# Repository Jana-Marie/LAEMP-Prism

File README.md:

# LAEMP-Prism

The LÄMP-Prism is an aesthetically pleasing and colorful effect lamp that can be used in your home. It can be controlled using Zigbee (e.g., Philips Hue) and has RGBY + WW/CW LEDs, providing a wide dynamic range and fantastic color representation. The lamp can be soldered together at home or assembled by JLCPCB.

An inbuilt slow fade-animation creates plenty colored dots around the room, one can choose from three different animations by quickly bringing red from 0% to 100% and back three times. LAEMP will switch from static light, to slow-fading dots to being an RGB-beacon. Its most pleasing mode is the slow-fading animation. It is fast enough to raise the rooms texture, slow enough to not be irritating and just perfect for comfy nights.

The project consists of nine PCBs that are cleverly interlocked with pinheaders and capacitors. The Prism-like shape, combined with its 291 LEDs, projects a slightly changing dotted pattern into its environment.

<table>
  <tbody>
    <tr>
      <td>
        
      </td>
      <td>
        
      </td>
    </tr>
  </tbody>
</table>

This project is an attempt to add some colored lights and interesting patterns to ones home. I hope you enjoy it! :3

<table>
  <tbody>
    <tr>
      <td>
        
      </td>
      <td>
        
      </td>
    </tr>
  </tbody>
</table>

### V2

Please note that the E75-2G4M20S module is End of Life and is hard to obtain. I'm working on a V2.0 with STM32WB (see [MiniBee](https://github.com/Jana-Marie/MiniBee)). The Hex-Base-Board is henceforth subject to be updated, all other boards shouldnt change.

### Sister project

LAEMP-Prism is a sister project to [LAEMP-Panel](https://github.com/Jana-Marie/LAEMP-Panel)

## Concept

The overall concept was developed in OpenSCAD and a pseudo-random pattern of circles was choosen for the walls. If one wants to put effort into this project, different walls can be used. The standard base-to-wall-interface also allows for much different and custom walls. E.g. hexagonal holes, shorter or taller walls, bended walls, ...

## Build

This build is definitely time-consuming, as each LAEMP Prism features 291 LEDs, and therefore requires at least 291 100nF capacitors. Additionally, the wall PCBs are rather thin and long, making reflow difficult and assembly time-consuming.

Once all eight boards are assembled (the top board has no components ^⁻^), they can be interlocked with one another. To do this, begin by plugging the LED-Base-Board into the Base-Board, and then carefully plugging wall after wall into the baseboard. Try to put the Top-Board onto the build after assembling five boards. The board with the Type-C cutout should not be the last board to assemble. Finally, try to plug in the last board. This step can be quite tricky and may require a few attempts. Once all boards are assembled, align all walls with each other and place the whole board onto the 3D printed base.

You will need the following set of baords for a build:

 - 1 x Base-Board
 - 1 x Base-LED-Board
 - 1 x Top-Board
 - 5 x Wall-Board
 - 1 x USB-Wall-Board

<table>
  <tbody>
    <tr>
      <td>
        
      </td>
      <td>
        
      </td>
    </tr>
    <tr>
      <td>
        
      </td>
      <td>
        
      </td>
    </tr>
  </tbody>
</table>

## Firmware

There are two firmwares to be flashed, one for the ESP32 and one for the E75-2G4M20S.

### ESP32

This is a simple Arduino project and can be flashed via Arduino (initially built on Arduino 1.8.19).

### E75

Please refer to the awesome works of [PeeVeeOne](https://peeveeone.com/zll-tldr/) to flash `Light_ColorLight_JN5168_RGB` onto the E75-2G4M20S module.

## Todo

 - [ ] Bug: Animation selector sucks, it gets stuck on states, needs fix.
 - [ ] Bug: Color wheel is off
 - [ ] Update to baseboard v2

## Folder Structure

```
 - 3D/               3D-Printable base, Concept
 - design/           assets, renders
 - images/           images for README
 - laemp_base/       base board hosting the MCU(s)
 - laemp_led_board/  LED base board, plugs directly ontop of the base board
 - laemp_top/        top board, has no electrical functionality, just mechanical
 - laemp_wall/       wall board, hosting 41 leds each
 - laemp_wall_usb/   same wall board, but with USB cutout
 - firmware/
   - leamp_prism/    ESP32 FW
   - zigbee/         E75 FW
```

## License

Copyright Jana Marie Hemsing 2023.
This source describes Open Hardware and is licensed under the CERN-
OHL-S v2.

You may redistribute and modify this source and make products using it
under the terms of the CERN-OHL-S v2
([LICENSE](/LICENSE)).

This source is distributed WITHOUT ANY EXPRESS OR IMPLIED
WARRANTY, INCLUDING OF MERCHANTABILITY, SATISFACTORY
QUALITY AND FITNESS FOR A PARTICULAR PURPOSE. Please see
the CERN-OHL-S v2 for applicable conditions.

Source location: https://github.com/Jana-Marie/LAEMP-Prism/
As per CERN-OHL-S v2 section 4, should You produce hardware based
on this source, You must where practicable maintain the Source Location
visible on the external case of LAEMP-Prism or other products you make using
this source

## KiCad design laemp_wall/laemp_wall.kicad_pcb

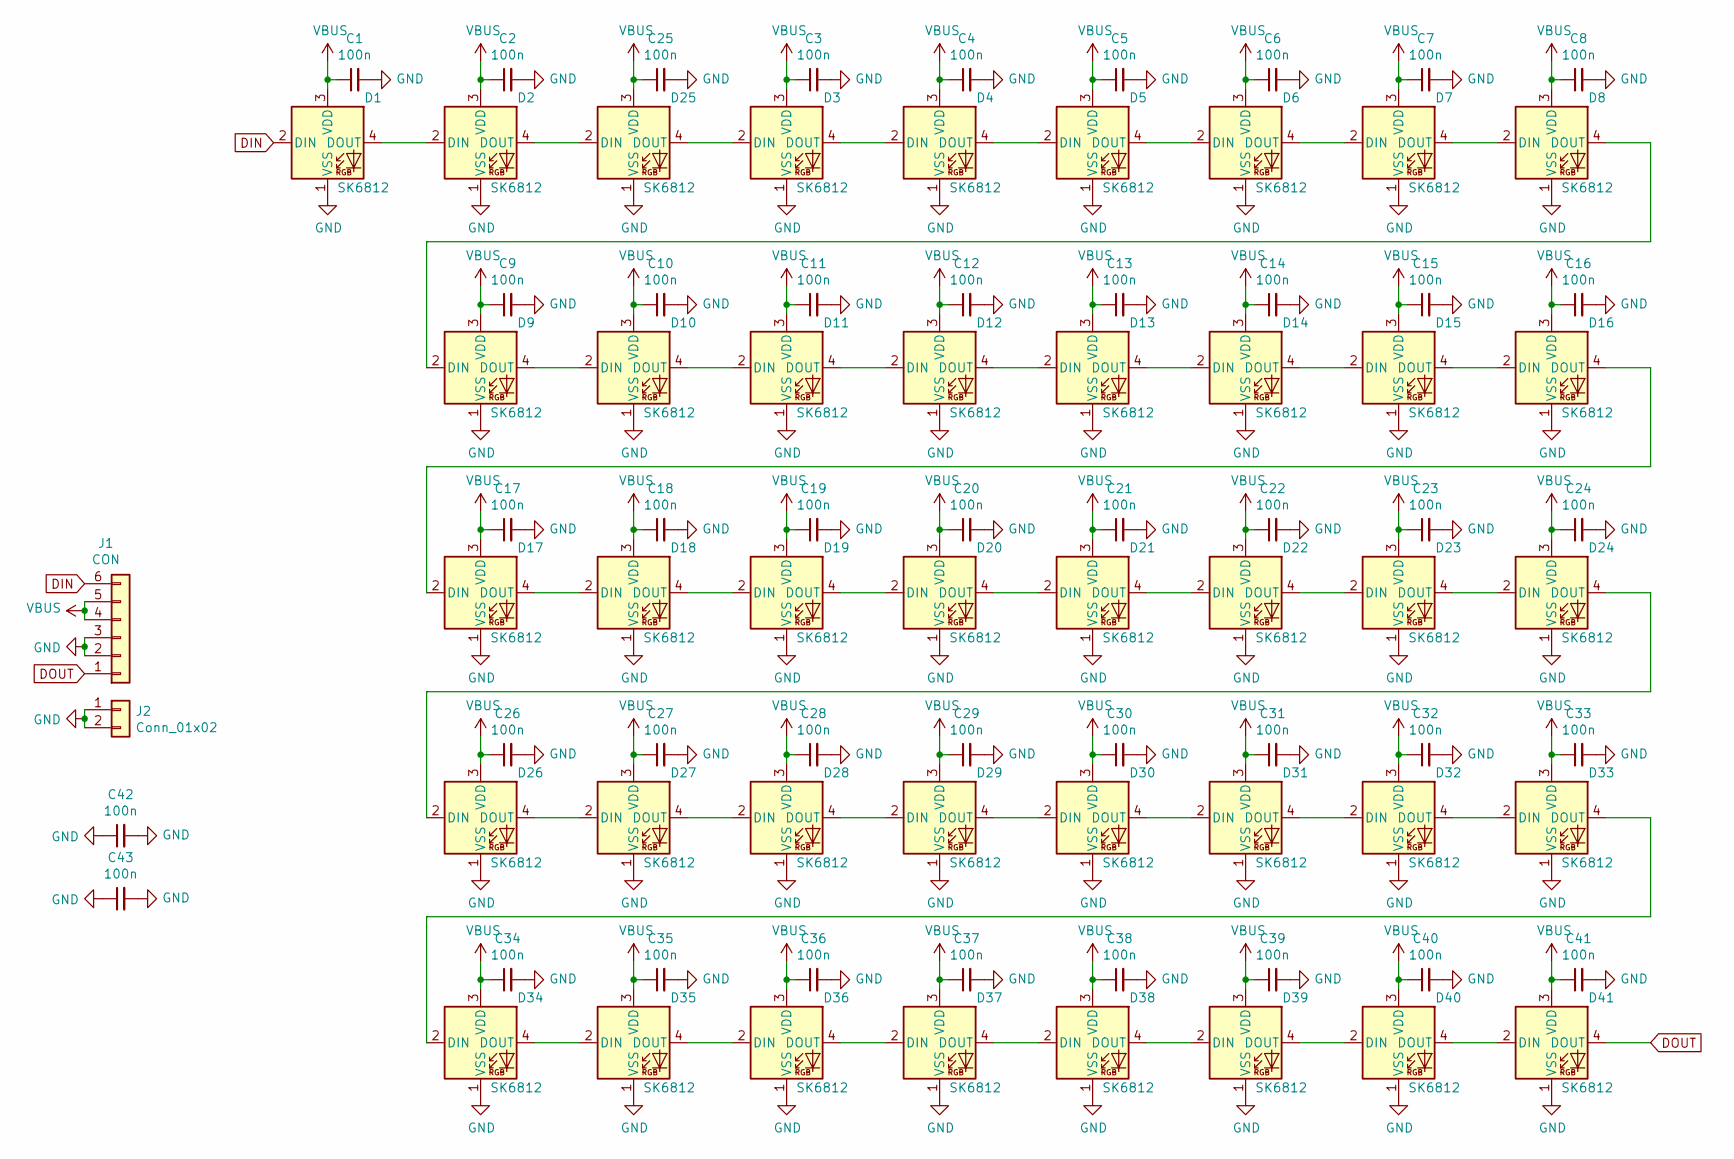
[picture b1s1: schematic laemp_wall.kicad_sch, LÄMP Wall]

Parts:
C1, C2, C3, C4, C5, C6, C7, C8, C9, C10, C11, C12, C13, C14, C15, C16, C17, C18, C19, C20, C21, C22, C23, C24, C25, C26, C27, C28, C29, C30, C31, C32, C33, C34, C35, C36, C37, C38, C39, C40, C41, C42, C43: 100n; C_0402
D1, D2, D3, D4, D5, D6, D7, D8, D9, D10, D11, D12, D13, D14, D15, D16, D17, D18, D19, D20, D21, D22, D23, D24, D25, D26, D27, D28, D29, D30, D31, D32, D33, D34, D35, D36, D37, D38, D39, D40, D41: SK6812; LED_SK6812_PLCC4_5.0x5.0mm_P3.2mm
J1: CON; conn_01x06_smd_2mm
J2: Conn_01x02; conn_01x02_smd_2mm

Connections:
DIN: D1.2 (DIN), J1.6
DOUT: D41.4 (DOUT), J1.1
GND: C1.2, C2.2, C3.2, C4.2, C5.2, C6.2, C7.2, C8.2, C9.2, C10.2, C11.2, C12.2, C13.2, C14.2, C15.2, C16.2, C17.2, C18.2, C19.2, C20.2, C21.2, C22.2, C23.2, C24.2, C25.2, C26.2, C27.2, C28.2, C29.2, C30.2, C31.2, C32.2, C33.2, C34.2, C35.2, C36.2, C37.2, C38.2, C39.2, C40.2, C41.2, C42.1, C42.2, C43.1, C43.2, D1.1 (VSS), D2.1 (VSS), D3.1 (VSS), D4.1 (VSS), D5.1 (VSS), D6.1 (VSS), D7.1 (VSS), D8.1 (VSS), D9.1 (VSS), D10.1 (VSS), D11.1 (VSS), D12.1 (VSS), D13.1 (VSS), D14.1 (VSS), D15.1 (VSS), D16.1 (VSS), D17.1 (VSS), D18.1 (VSS), D19.1 (VSS), D20.1 (VSS), D21.1 (VSS), D22.1 (VSS), D23.1 (VSS), D24.1 (VSS), D25.1 (VSS), D26.1 (VSS), D27.1 (VSS), D28.1 (VSS), D29.1 (VSS), D30.1 (VSS), D31.1 (VSS), D32.1 (VSS), D33.1 (VSS), D34.1 (VSS), D35.1 (VSS), D36.1 (VSS), D37.1 (VSS), D38.1 (VSS), D39.1 (VSS), D40.1 (VSS), D41.1 (VSS), J1.2, J1.3, J2.1, J2.2
unnamed: D1.4 (DOUT), D2.2 (DIN)
unnamed: D2.4 (DOUT), D25.2 (DIN)
unnamed: D3.4 (DOUT), D4.2 (DIN)
unnamed: D4.4 (DOUT), D5.2 (DIN)
unnamed: D5.4 (DOUT), D6.2 (DIN)
unnamed: D6.4 (DOUT), D7.2 (DIN)
unnamed: D7.4 (DOUT), D8.2 (DIN)
unnamed: D8.4 (DOUT), D9.2 (DIN)
unnamed: D9.4 (DOUT), D10.2 (DIN)
unnamed: D10.4 (DOUT), D11.2 (DIN)
unnamed: D11.4 (DOUT), D12.2 (DIN)
unnamed: D12.4 (DOUT), D13.2 (DIN)
unnamed: D13.4 (DOUT), D14.2 (DIN)
unnamed: D14.4 (DOUT), D15.2 (DIN)
unnamed: D15.4 (DOUT), D16.2 (DIN)
unnamed: D16.4 (DOUT), D17.2 (DIN)
unnamed: D17.4 (DOUT), D18.2 (DIN)
unnamed: D18.4 (DOUT), D19.2 (DIN)
unnamed: D19.4 (DOUT), D20.2 (DIN)
unnamed: D20.4 (DOUT), D21.2 (DIN)
unnamed: D21.4 (DOUT), D22.2 (DIN)
unnamed: D22.4 (DOUT), D23.2 (DIN)
unnamed: D23.4 (DOUT), D24.2 (DIN)
unnamed: D24.4 (DOUT), D26.2 (DIN)
unnamed: D3.2 (DIN), D25.4 (DOUT)
unnamed: D26.4 (DOUT), D27.2 (DIN)
unnamed: D27.4 (DOUT), D28.2 (DIN)
unnamed: D28.4 (DOUT), D29.2 (DIN)
unnamed: D29.4 (DOUT), D30.2 (DIN)
unnamed: D30.4 (DOUT), D31.2 (DIN)
unnamed: D31.4 (DOUT), D32.2 (DIN)
unnamed: D32.4 (DOUT), D33.2 (DIN)
unnamed: D33.4 (DOUT), D34.2 (DIN)
unnamed: D34.4 (DOUT), D35.2 (DIN)
unnamed: D35.4 (DOUT), D36.2 (DIN)
unnamed: D36.4 (DOUT), D37.2 (DIN)
unnamed: D37.4 (DOUT), D38.2 (DIN)
unnamed: D38.4 (DOUT), D39.2 (DIN)
unnamed: D39.4 (DOUT), D40.2 (DIN)
unnamed: D40.4 (DOUT), D41.2 (DIN)
VBUS: C1.1, C2.1, C3.1, C4.1, C5.1, C6.1, C7.1, C8.1, C9.1, C10.1, C11.1, C12.1, C13.1, C14.1, C15.1, C16.1, C17.1, C18.1, C19.1, C20.1, C21.1, C22.1, C23.1, C24.1, C25.1, C26.1, C27.1, C28.1, C29.1, C30.1, C31.1, C32.1, C33.1, C34.1, C35.1, C36.1, C37.1, C38.1, C39.1, C40.1, C41.1, D1.3 (VDD), D2.3 (VDD), D3.3 (VDD), D4.3 (VDD), D5.3 (VDD), D6.3 (VDD), D7.3 (VDD), D8.3 (VDD), D9.3 (VDD), D10.3 (VDD), D11.3 (VDD), D12.3 (VDD), D13.3 (VDD), D14.3 (VDD), D15.3 (VDD), D16.3 (VDD), D17.3 (VDD), D18.3 (VDD), D19.3 (VDD), D20.3 (VDD), D21.3 (VDD), D22.3 (VDD), D23.3 (VDD), D24.3 (VDD), D25.3 (VDD), D26.3 (VDD), D27.3 (VDD), D28.3 (VDD), D29.3 (VDD), D30.3 (VDD), D31.3 (VDD), D32.3 (VDD), D33.3 (VDD), D34.3 (VDD), D35.3 (VDD), D36.3 (VDD), D37.3 (VDD), D38.3 (VDD), D39.3 (VDD), D40.3 (VDD), D41.3 (VDD), J1.4, J1.5

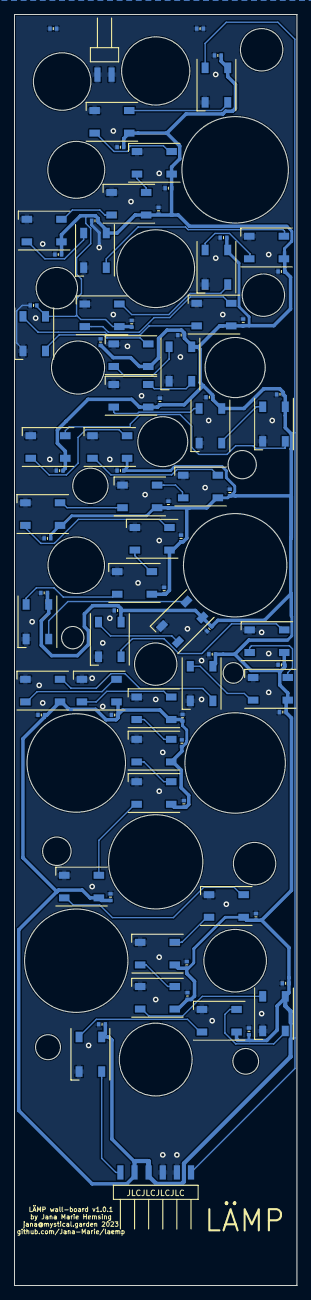
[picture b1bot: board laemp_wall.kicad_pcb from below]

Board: 2 copper layers, 40.0 x 180.0 mm, 86 parts (86 on the bottom side), 44 nets.

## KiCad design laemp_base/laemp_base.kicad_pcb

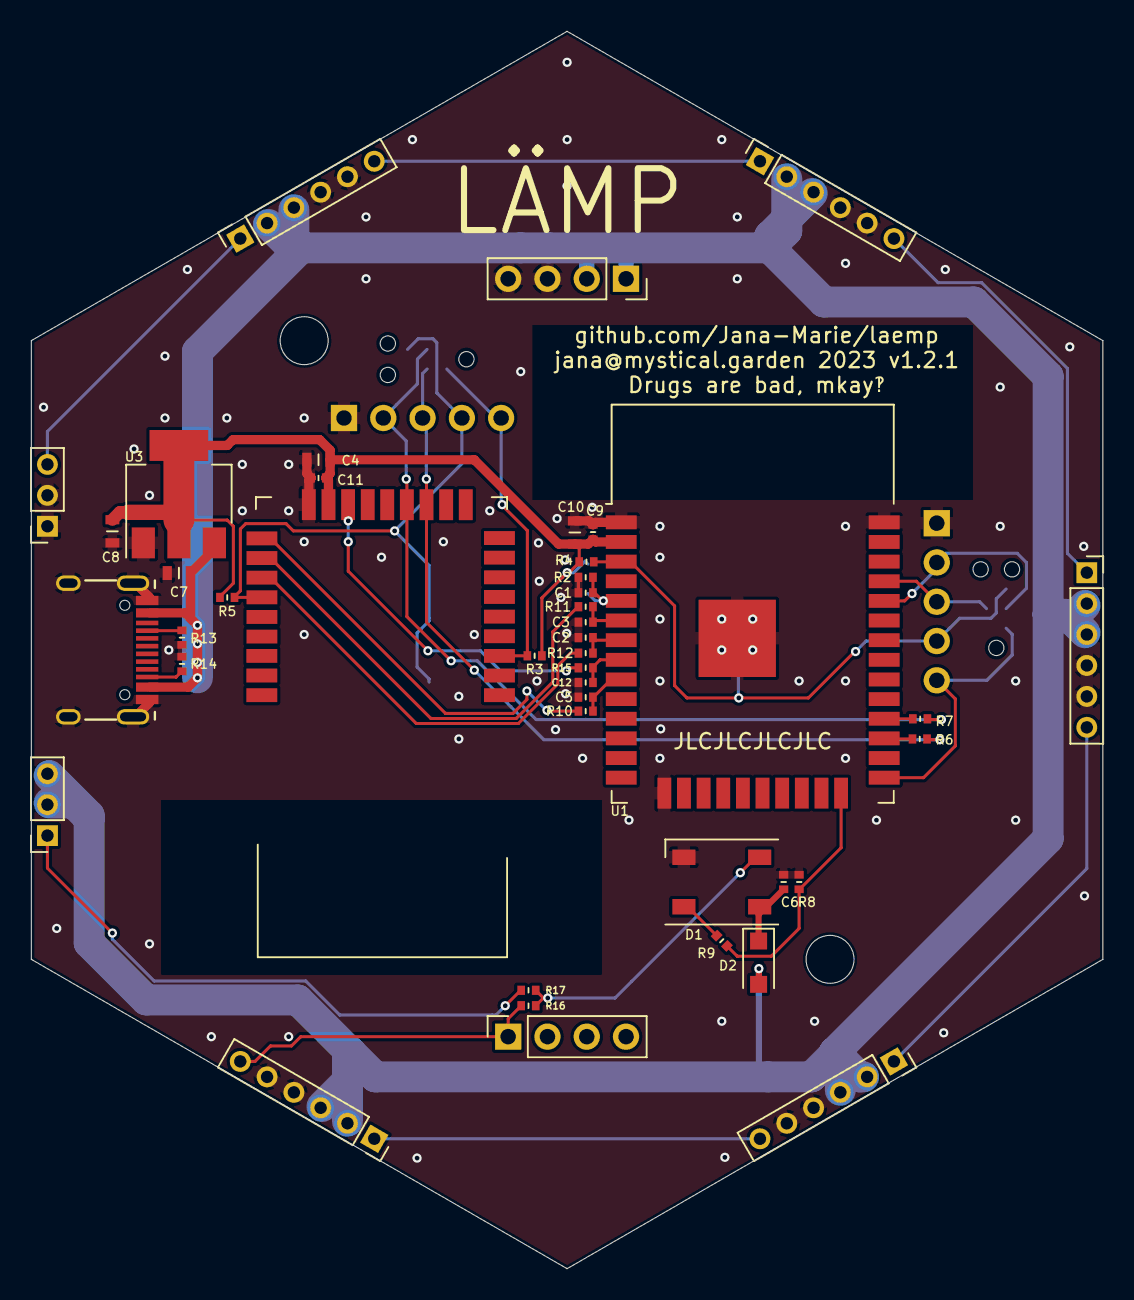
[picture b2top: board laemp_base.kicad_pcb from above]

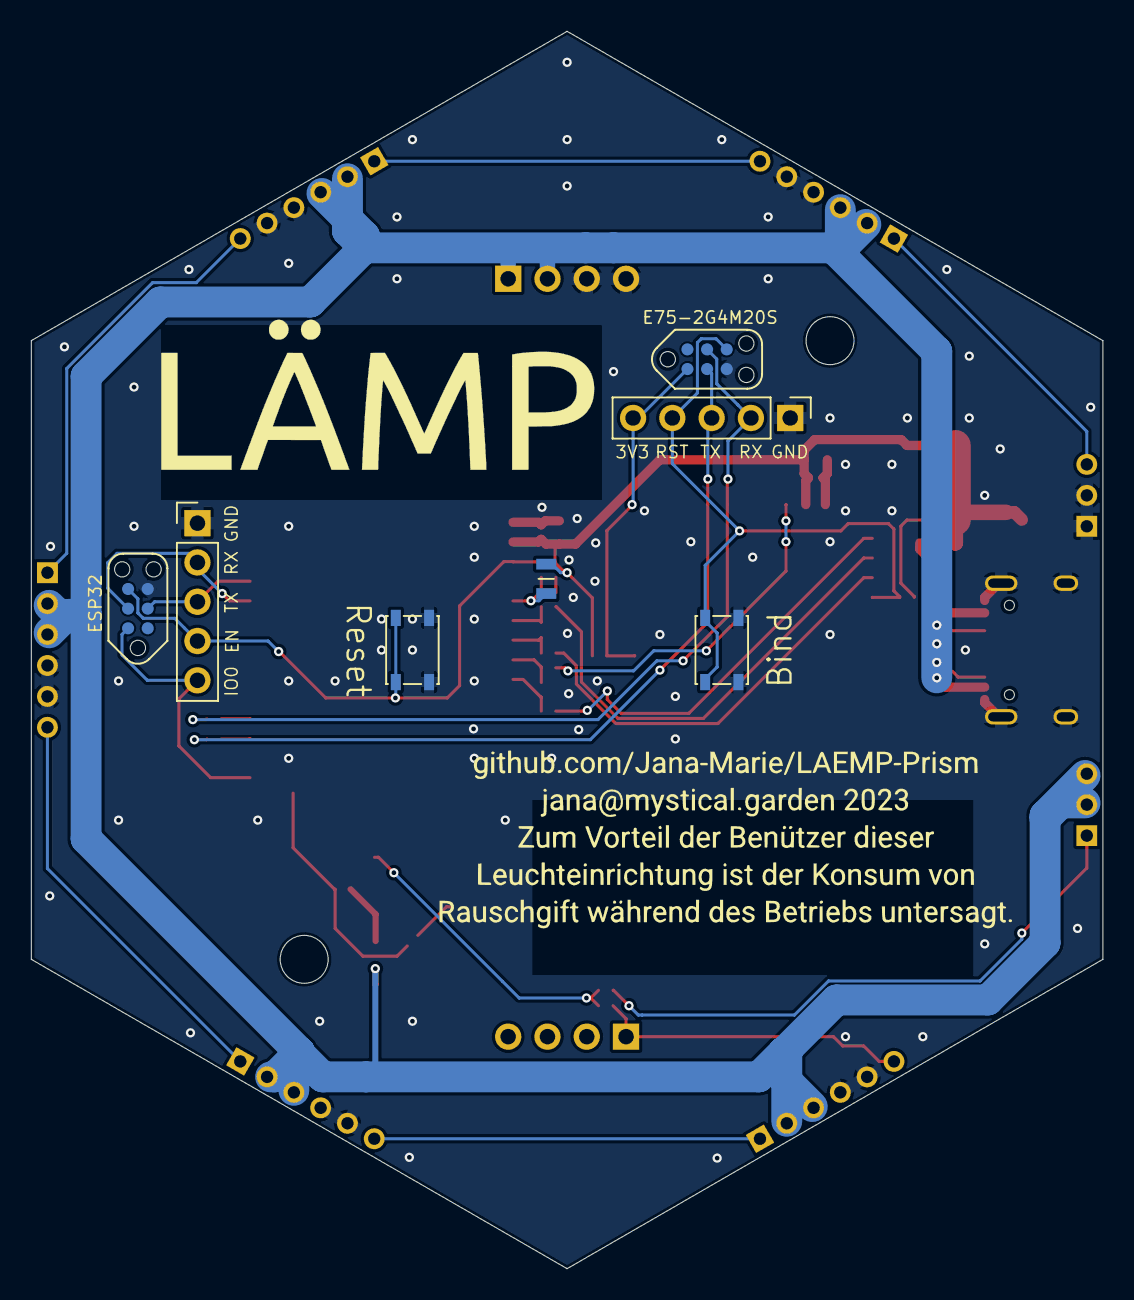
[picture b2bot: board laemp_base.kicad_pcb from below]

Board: 2 copper layers, 69.3 x 80.0 mm, 50 parts (7 on the bottom side), 35 nets.

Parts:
C1, C2, C3, C5, C6, C9, C11, C12: 100n; C_0402
C4, C7, C8, C10: 10u; C_0603
D1: SK6812; LED_SK6812_PLCC4_5.0x5.0mm_P3.2mm
D2: D_Small; D_SOD-123F
J1: ESP_proc; PinHeader_1x05_P2.54mm_Vertical
J2: E75_proc; PinHeader_1x05_P2.54mm_Vertical
J3: USB_C; USB-C 16Pin
J4, J5: PANEL0; PinSocket_1x03_P2.00mm_Vertical
J6: PANEL1; PinSocket_1x06_P2.00mm_Vertical_center
J7: PANEL2; PinSocket_1x06_P2.00mm_Vertical_center
J8: PANEL3; PinSocket_1x06_P2.00mm_Vertical_center
J9: PANEL4; PinSocket_1x06_P2.00mm_Vertical_center
J10: PANEL5; PinSocket_1x06_P2.00mm_Vertical_center
J11: LED_HEX0; PinSocket_1x04_P2.54mm_Vertical_center
J12: LED_HEX1; PinSocket_1x04_P2.54mm_Vertical_center
P1: TC2030-ESP; TC2030
P2: TC2030-E75; TC2030
R1: R_PHOTO; R_0805
R2, R8, R10, R11, R12, R15: 100k; R_0402
R3, R4, R5, R6, R7, R13, R14: 5k1; R_0402
R9, R17: 20; R_0402
R16: DNP; R_0402
SW1: RST; SW_SPST_PTS810
SW2: BIND; SW_SPST_PTS810
U1: ESP32-WROOM-32
U2: E75-2G4M20S; E75-2G4M10S
U3: AMS1117-3.3; SOT-223-3_TabPin2

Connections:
+3V3: C4.1, C8.1, C9.1, C10.1, C11.1, R1.1, R3.1, R4.1, R5.1, U1.2 (VDD), U2.17 (VDD), U3.2 (VO)
DOUT: J10.6, J12.1, R16.1
D_P0_P1: J5.3, J6.1
D_P1_P2: J6.6, J7.1
D_P2_P3: J7.6, J8.1
D_P3_P4: J8.6, J9.1
D_P4_P5: J9.6, J10.1
E75_RST: J2.4, P2.6 (EN), R5.2, SW2.2, U2.22 (RST)
E75_RX: J2.2, P2.4 (RXD), R7.2, U2.13 (RXD_IO7)
E75_TX: J2.3, P2.3 (TXD), R6.2, U2.12 (TXD_IO6)
ESP_EN: J1.4, P1.6 (EN), R4.2, SW1.2, U1.3 (EN)
ESP_IO0: J1.5, P1.2 (IO0), U1.25 (IO0)
ESP_RX: J1.2, P1.4 (RXD), U1.34 (RXD0/IO3)
ESP_TX: J1.3, P1.3 (TXD), U1.35 (TXD0/IO1)
GND: C1.2, C2.2, C3.2, C4.2, C5.2, C6.1, C7.2, C8.2, C9.2, C10.2, C11.2, C12.2, D1.1 (VSS), J1.1, J2.1, J3.A1 (GND), J3.A12 (GND), J3.B1 (GND), J3.B12 (GND), J3.S1 (SHIELD), J5.1, J5.2, J6.4, J6.5, J7.4, J7.5, J8.4, J8.5, J9.4, J9.5, J10.4, J10.5, J11.3, J11.4, P1.5 (GND), P2.5 (GND), R2.1, R8.1, R13.2, R14.2, SW1.1, SW2.1, U1.1 (GND), U1.15 (GND), U1.38 (GND), U1.39 (GND), U2.18 (GND), U3.1 (GND)
unnamed: C1.1, R1.2, R2.2, U1.5 (SENSOR_VN)
unnamed: C2.1, R12.1, U1.7 (IO35)
unnamed: C3.1, R11.1, U1.6 (IO34)
unnamed: C5.1, R10.1, U1.9 (IO33)
unnamed: C6.2, D1.3 (VDD), D2.1 (K)
unnamed: C12.1, R15.1, U1.8 (IO32)
unnamed: D1.2 (DIN), R9.1
unnamed: D1.4 (DOUT), R16.2, R17.2
unnamed: J2.5, P2.1 (VCC/NC), R3.2, U2.3 (SPI_MISO)
unnamed: J3.A5 (CC1), R13.1
unnamed: J3.B5 (CC2), R14.1
unnamed: R6.1, U1.27 (IO16)
unnamed: R7.1, U1.28 (IO17)
unnamed: R8.2, R9.2, U1.24 (IO2)
PWM_1: R15.2, U2.16 (IO10)
PWM_B: R12.2, U2.21 (IO13)
PWM_G: R11.2, U2.20 (IO12)
PWM_R: R10.2, U2.19 (IO11)
SK6812: J4.1, R17.1
VBUS: C7.1, D2.2 (A), J3.A4 (VBUS), J3.A9 (VBUS), J3.B4 (VBUS), J3.B9 (VBUS), J4.2, J4.3, J6.2, J6.3, J7.2, J7.3, J8.2, J8.3, J9.2, J9.3, J10.2, J10.3, J11.1, J11.2, U3.3 (VI)

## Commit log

2023-03-02 added images
2023-03-02 added assets
2023-03-02 added 3D files
2023-03-02 added gitignore
2023-03-02 added license
2023-03-02 updated gitignore
2023-03-02 added base
2023-03-02 added led baord
2023-03-02 rm cache.lib
2023-03-02 added top
2023-03-02 added walls
2023-03-02 rename
2023-03-02 added FW
2023-03-02 updaed readme
2023-03-02 I amm very good with Markdown
2023-03-02 updated bottom text
2023-03-02 updated project file
